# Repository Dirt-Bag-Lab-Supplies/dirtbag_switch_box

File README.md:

# dirtbag_switch_box
RV Electrical Systems

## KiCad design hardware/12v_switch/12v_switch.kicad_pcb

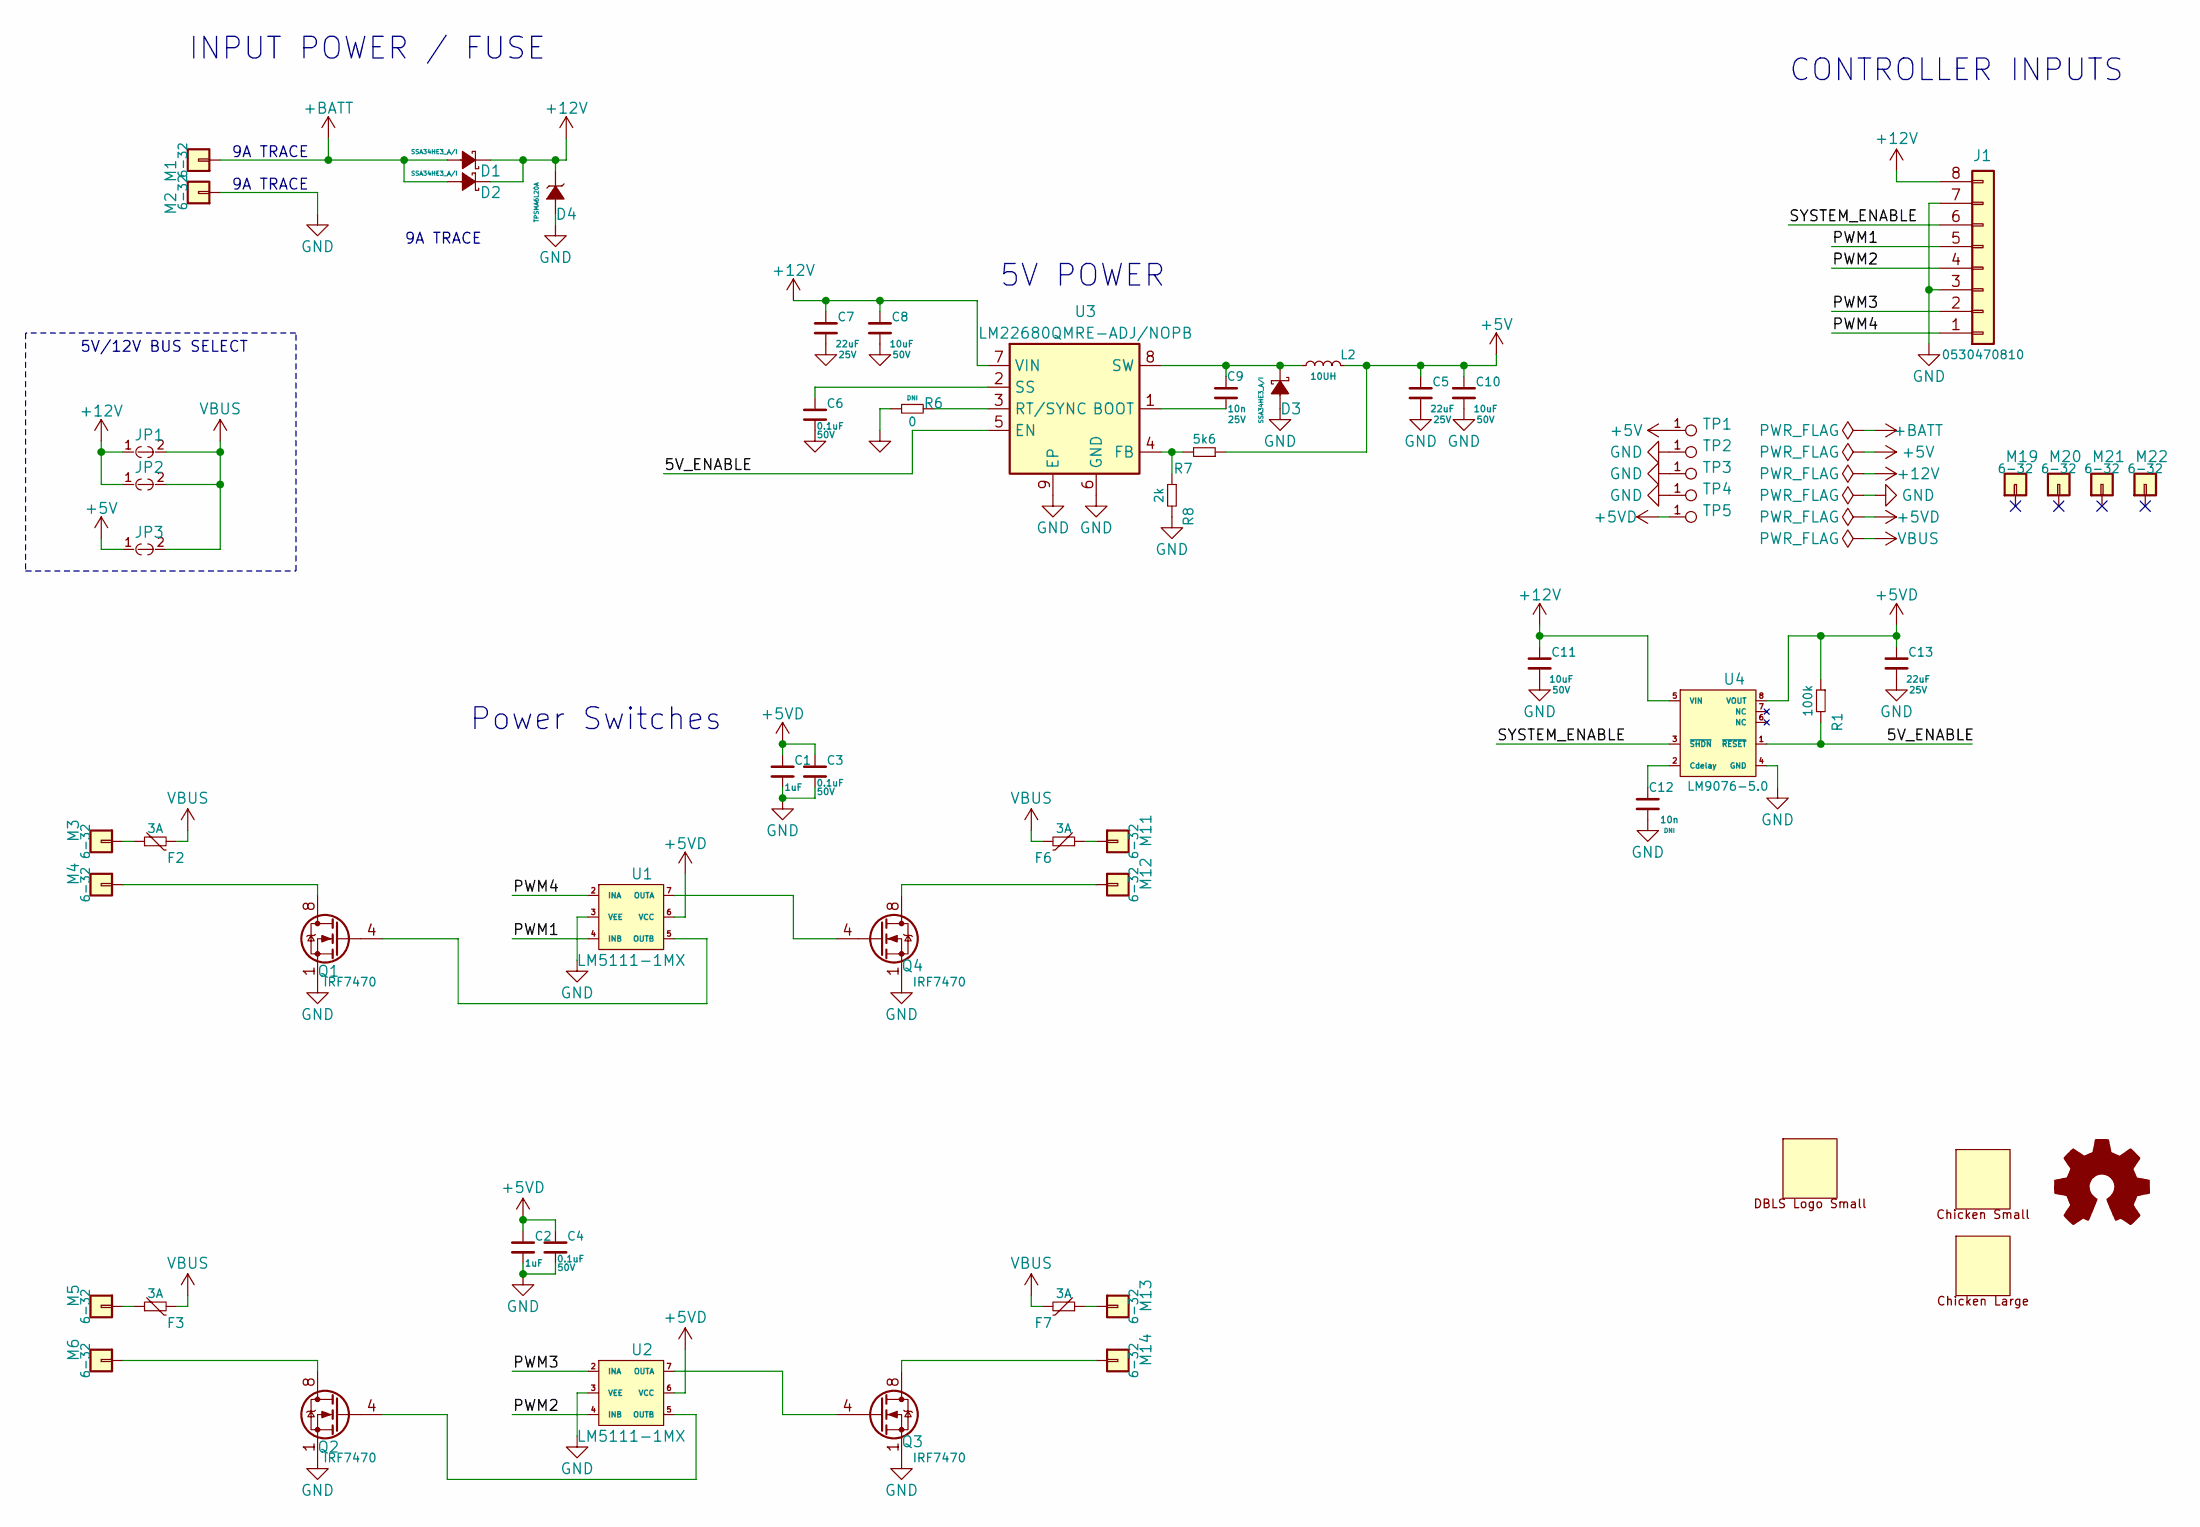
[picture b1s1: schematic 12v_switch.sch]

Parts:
C1, C2: SMD-CAP-1UF-0402; C_0402_1005Metric; mfg_pn GRM155R61E105KA12D
C3, C4, C6: MURATA_GRM155R71H104ME14J; C_0402; voltage 50V; mfg_pn GRM155R71H104ME14J
C5, C7, C13: MURATA_GRM31CC81E226KE11L; C_1206; voltage 25V; mfg_pn GRM31CC81E226KE11L
C8, C10, C11: MURATA_GRT31CR61H106KE01L; C_1206; voltage 50V; mfg_pn GRT31CR61H106KE01L
C9, C12: MURATA_GCM155R71E103KA37D; C_0402; voltage 25V; mfg_pn GCM155R71E103KA37D
D1, D2, D3: VISHAY_SSA34HE3_A_I; D_SMA; mfg_pn SSA34HE3_A/I
D4: LITTLEFUSE_TPSMA6L20A; D_SMA; mfg_pn TPSMA6L20A
F2, F3, F6, F7: LITTLEFUSE_RGEF300-2; LITTLEFUSE_RGEF; mfg_pn RGEF300-2
J1: MOLEX_0530470810; Molex_PicoBlade_53047-0810_08x1.25mm_Straight; mfg_pn 0530470810
JP1, JP2, JP3: PAD_JUMPER_2PIN_NC
L2: PANASONIC_ETQ-P3M100KVN; L_6.4x6.0_H3; mfg_pn ETQ-P3M100KVN
LOGO1: DBLS_Chicken_Small; Rooster_4mmx4mm
LOGO2: DBLS_Chicken_Large; Rooster_43mmx43mm
LOGO4: DBLS_van_logo_small_v1; van_logo_small
M1, M2, M3, M4, M5, M6, M11, M12, M13, M14: SCREW_6-32_POWER
M19, M20, M21, M22: SCREW_6-32_NORMAL
Q1, Q2, Q3, Q4: INFINEON_IRF7470TRPBF; SOIC-8_3.9x4.9mm_Pitch1.27mm; mfg_pn IRF7470TRPBF
R1: VISHAYDALE_CRCW0402100KJNEDC; R_0402; mfg_pn CRCW0402100KJNEDC
R6: VISHAYDALE_CRCW04020000Z0EDHP; R_0402; mfg_pn CRCW04020000Z0EDHP
R7: VISHAYDALE_CRCW04025K60JNED; R_0402; mfg_pn CRCW04025K60JNED
R8: VISHAYDALE_CRCW04022K00JNEDC; R_0402; mfg_pn CRCW04022K00JNEDC
TP1, TP2, TP3, TP4, TP5: DBLS_TESTPOINT_NORMAL; DBLS_Testpoint_Normal
U1, U2: TI_LM5111-1MX_NOPB; SOIC-8_3.9x4.9mm_Pitch1.27mm; mfg_pn LM5111-1MX/NOPB
U3: TI_LM22680QMRE-ADJ; SOIC-8-1EP_3.9x4.9mm_Pitch1.27mm_ALT; mfg_pn LM22680QMRE-ADJ/NOPB
U4: TI_LM9076BMA-5.0; SOIC-8_3.9x4.9mm_Pitch1.27mm; mfg_pn LM9076BMA-5.0/NOPB

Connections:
+5V: C5.1, C10.1, JP3.1, L2.2, R7.1, TP1.1
+5VD: C1.1, C2.1, C3.1, C4.1, C13.1, R1.1, TP5.1, U1.6 (VCC), U2.6 (VCC), U4.8 (VOUT)
+12V: C7.1, C8.1, C11.1, D1.1 (K), D2.1 (K), D4.1 (K), J1.8, JP1.1, JP2.1, U3.7 (VIN), U4.5 (VIN)
+BATT: D1.2 (A), D2.2 (A), M1.1
/5V_ENABLE: R1.2, U3.5 (EN), U4.1 (~RESET)
/PWM1: J1.5, U1.4 (INB)
/PWM2: J1.4, U2.4 (INB)
/PWM3: J1.2, U2.2 (INA)
/PWM4: J1.1, U1.2 (INA)
/SYSTEM_ENABLE: J1.6, U4.3 (~SHDN)
GND: C1.2, C2.2, C3.2, C4.2, C5.2, C6.2, C7.2, C8.2, C10.2, C11.2, C12.2, C13.2, D3.2 (A), D4.2 (A), J1.3, J1.7, M2.1, Q1.1 (S), Q1.2 (S), Q1.3 (S), Q2.1 (S), Q2.2 (S), Q2.3 (S), Q3.1 (S), Q3.2 (S), Q3.3 (S), Q4.1 (S), Q4.2 (S), Q4.3 (S), R6.1, R8.2, TP2.1, TP3.1, TP4.1, U1.3 (VEE), U2.3 (VEE), U3.6 (GND), U3.9 (EP), U4.4 (GND)
unnamed: C6.1, U3.2 (SS)
unnamed: C9.1, D3.1 (K), L2.1, U3.8 (SW)
unnamed: C9.2, U3.1 (BOOT)
unnamed: C12.1, U4.2 (Cdelay)
unnamed: F2.1, M3.1
unnamed: F3.1, M5.1
unnamed: F6.1, M11.1
unnamed: F7.1, M13.1
unnamed: M4.1, Q1.5 (D), Q1.6 (D), Q1.7 (D), Q1.8 (D)
unnamed: M6.1, Q2.5 (D), Q2.6 (D), Q2.7 (D), Q2.8 (D)
unnamed: M12.1, Q4.5 (D), Q4.6 (D), Q4.7 (D), Q4.8 (D)
unnamed: M14.1, Q3.5 (D), Q3.6 (D), Q3.7 (D), Q3.8 (D)
unnamed: Q1.4 (G), U1.5 (OUTB)
unnamed: Q2.4 (G), U2.5 (OUTB)
unnamed: Q3.4 (G), U2.7 (OUTA)
unnamed: Q4.4 (G), U1.7 (OUTA)
unnamed: R6.2, U3.3 (RT/SYNC)
unnamed: R7.2, R8.1, U3.4 (FB)
VBUS: F2.2, F3.2, F6.2, F7.2, JP1.2, JP2.2, JP3.2

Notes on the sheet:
INPUT POWER / FUSE
9A TRACE
Power Switches
CONTROLLER INPUTS
5V POWER
5V/12V BUS SELECT

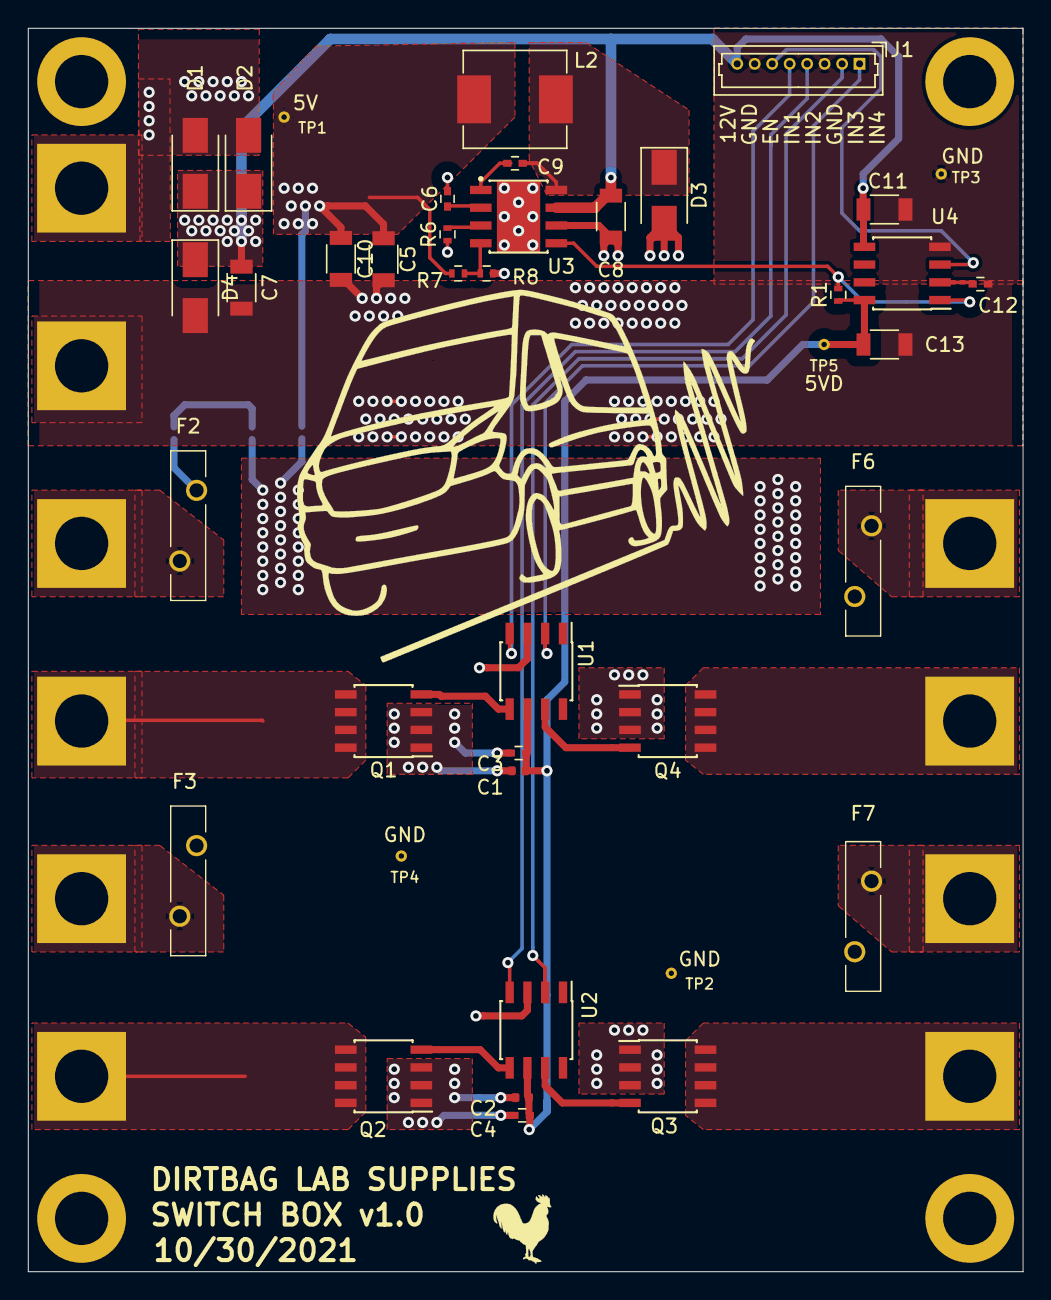
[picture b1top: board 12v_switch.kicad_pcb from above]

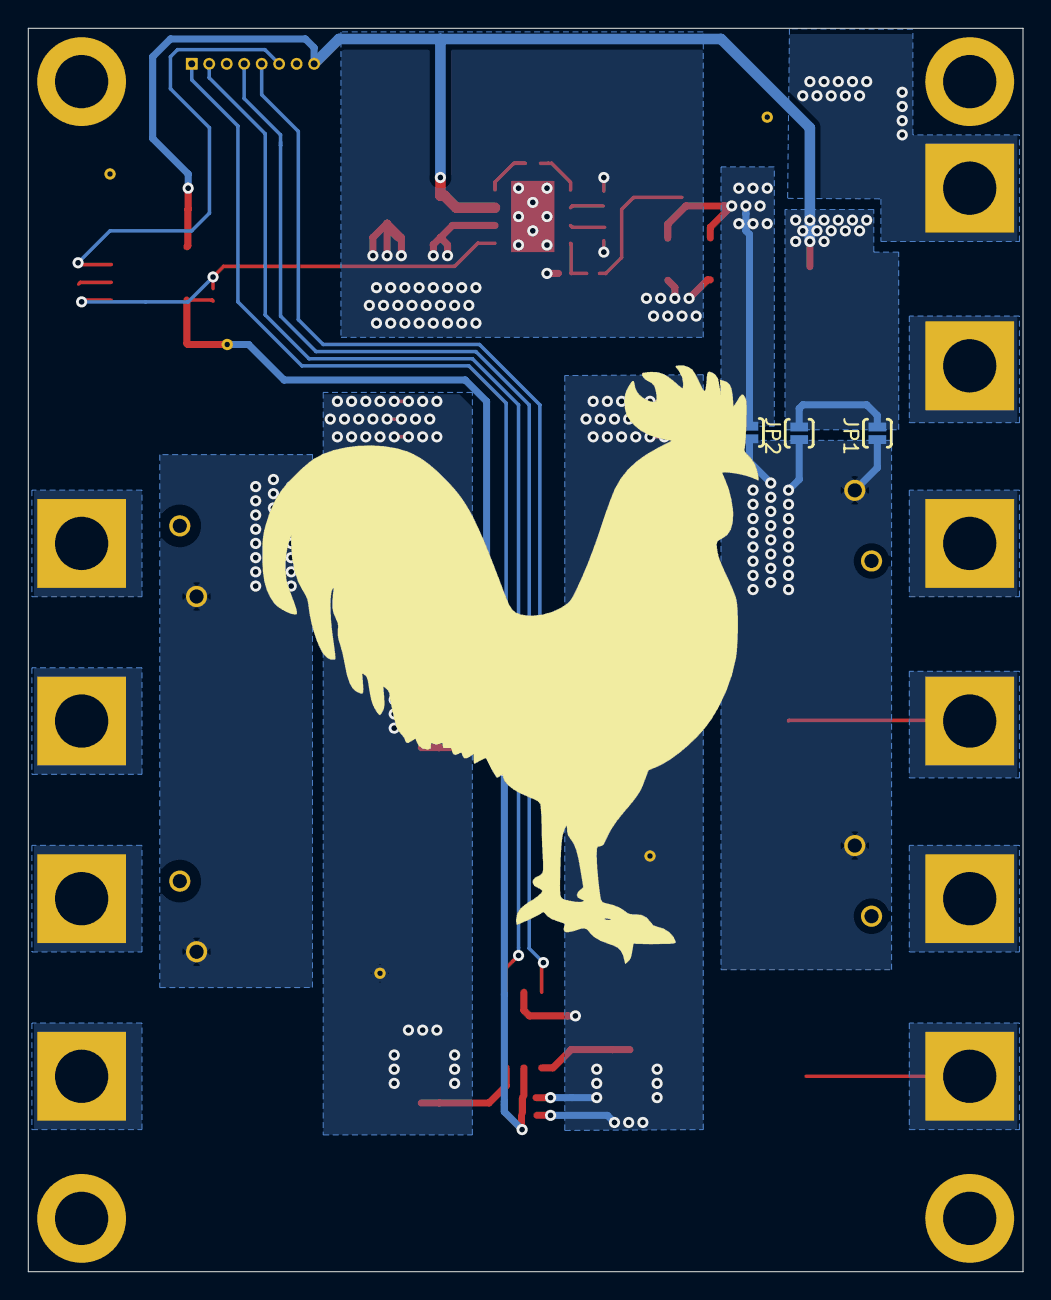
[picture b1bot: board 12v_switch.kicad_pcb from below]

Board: 2 copper layers, 71.1 x 88.9 mm, 60 parts (4 on the bottom side), 30 nets.

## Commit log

2021-10-17 Added project to git. Uses the Driver modules.
2021-10-17 Relayed layout with integrated drivers.
2021-10-18 Added fp lib and netlist. Saving before removing mcu.
2021-10-30 First draft layout with 4 switches + buck
2021-10-30 fixed designators. Added logo and labels
2021-10-30 Added interactive BOM.
2021-11-01 added reverse polarity, TVS, and better regulator bypass cap, and fixed feedback resistors
2021-11-01 Added separate 5V gate driver LDO
2021-12-15 added cad files for FreeCAD 0.19
2021-12-15 added step file for switchbox_v1.FCStd1
2021-12-18 added stl
